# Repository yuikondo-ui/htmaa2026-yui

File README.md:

# htmaa2026-yui

Yui Kondo's documentation site for *How to Make (Almost) Anything* (MIT MAS.863, Fall 2026).

**You write Markdown; `build.py` makes the site.** No framework — one Python script, one
CSS file. GitHub Actions rebuilds and deploys to GitHub Pages on every push to `main`.

## Layout

```
content/
  site.yml            name, banner text, email, repo link
  about.md            About page (two columns; split with a line containing only ---)
  final.md            Final project page
  weeks/weekNN.md     one file per week (01–15) — frontmatter + Markdown body
img/weekNN/           photos for that week (hero.jpg shows on the Grid + page top)
img/final/
files/weekNN/         design files (CAD, code, …)
css/style.css         all styling
build.py              Markdown → HTML
index.html grid.html about.html final.html weeks/*.html   ← generated, don't edit by hand
```

## Weekly routine

1. Drop photos into `img/weekNN/`. Keep them small (`sips -Z 1600 img/week01/*.jpg`).
2. Write `content/weeks/weekNN.md`. `##` headings become the left sidebar (見出し); `###` nest under them.
   Reference images as `img/weekNN/photo.jpg` — paths are fixed up for you.
3. Set `status: Done` in the frontmatter when finished.
4. Preview locally: `python3 build.py` then open `index.html`
   (first time: `pip install markdown`).
5. `git add -A && git commit -m "week NN" && git push` — Pages redeploys in ~1 minute.

### Week frontmatter

```
---
week: 03
date: 09/23
topics: [embedded programming](http://academy.cba.mit.edu/classes/embedded_programming/index.html)
recitation: electronics
status: WIP            # or Done
hero: img/week03/hero.jpg
summary: One line shown under the title.
---
```

`topics` (the class topics, with links) shows in the Index's middle column, the Grid caption
and the page's meta line. Optional `title:` adds your own name for the week to the page
heading (“Week 3 / title”); without it the heading is just “Week 3”.

## GitHub Pages setup (once)

Repo → Settings → Pages → *Build and deployment* → Source: **GitHub Actions**.
The workflow in `.github/workflows/pages.yml` does the rest.

## Fonts

| Use | Typeface | Status |
|-----|----------|--------|
| Name "Yui Kondo" in the header | **Gridular** (CoType Foundry, free, CC BY-ND 4.0) | Download from cotypefoundry.com/our-fonts/gridular and save as `fonts/Gridular-Regular.woff2` |
| Everything else | **ABC Diatype Variable** (ABC Dinamo, licensed) | Falls back to **Geist** (then Inter Tight) from Google Fonts unless `fonts/ABCDiatypeVariable.woff2` (+ `-Italic`) is present |
| Red banner | **ABC Diatype Extended Black Italic** | Falls back to **Archivo** Expanded Black Italic unless `fonts/ABCDiatypeExtended-BlackItalic.woff2` is present |

Until Gridular is added the name uses the body face. If your files are `.otf`/`.ttf`, either
change the `url(...)` in `css/style.css` or convert to woff2.
# mirror-extension

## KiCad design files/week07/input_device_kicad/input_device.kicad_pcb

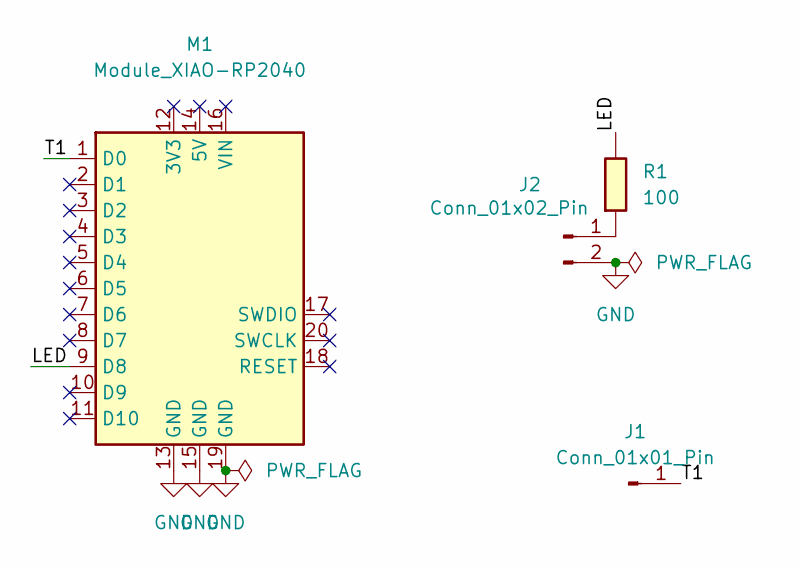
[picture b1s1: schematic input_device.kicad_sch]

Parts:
J1: Conn_01x01_Pin; PinHeader_01x01_P2.54mm_Horizontal_SMD
J2: Conn_01x02_Pin; PinHeader_01x02_P2.54mm_Horizontal_SMD
M1: Module_XIAO-RP2040; SeeedStudio_XIAO_RP2040
R1: 100; R_1206

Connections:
/<NO NET>: M1.10 (D9)
/<NO NET>_1: M1.10 (D9)
/LED: M1.9 (D8), R1.1
/T1: J1.1 (Pin_1_1), M1.1 (D0)
GND: J2.2, M1.13 (GND), M1.15 (GND), M1.19 (GND)
unnamed: J2.1, R1.2

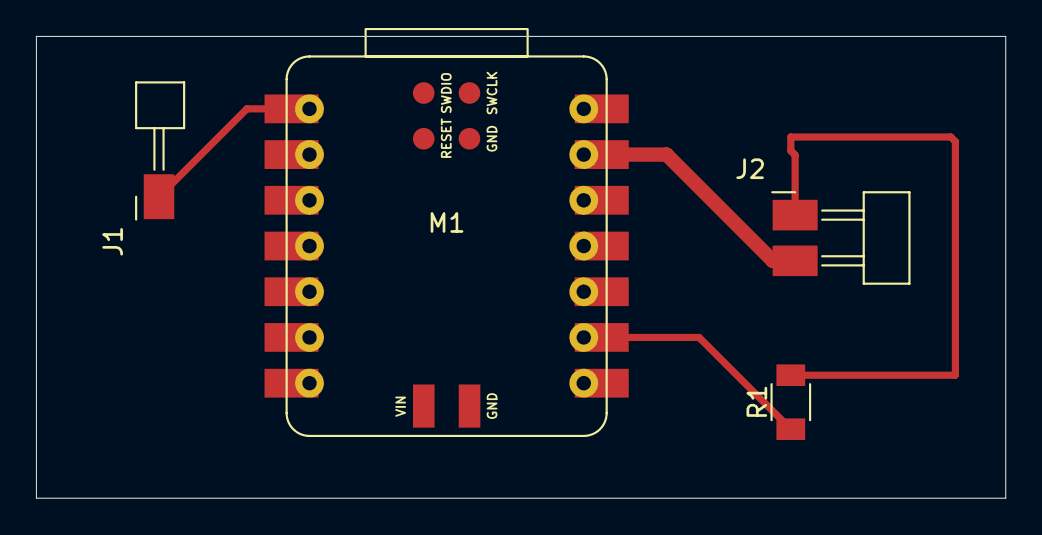
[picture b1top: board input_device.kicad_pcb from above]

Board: 2 copper layers, 53.8 x 25.7 mm, 4 parts (0 on the bottom side), 4 nets.

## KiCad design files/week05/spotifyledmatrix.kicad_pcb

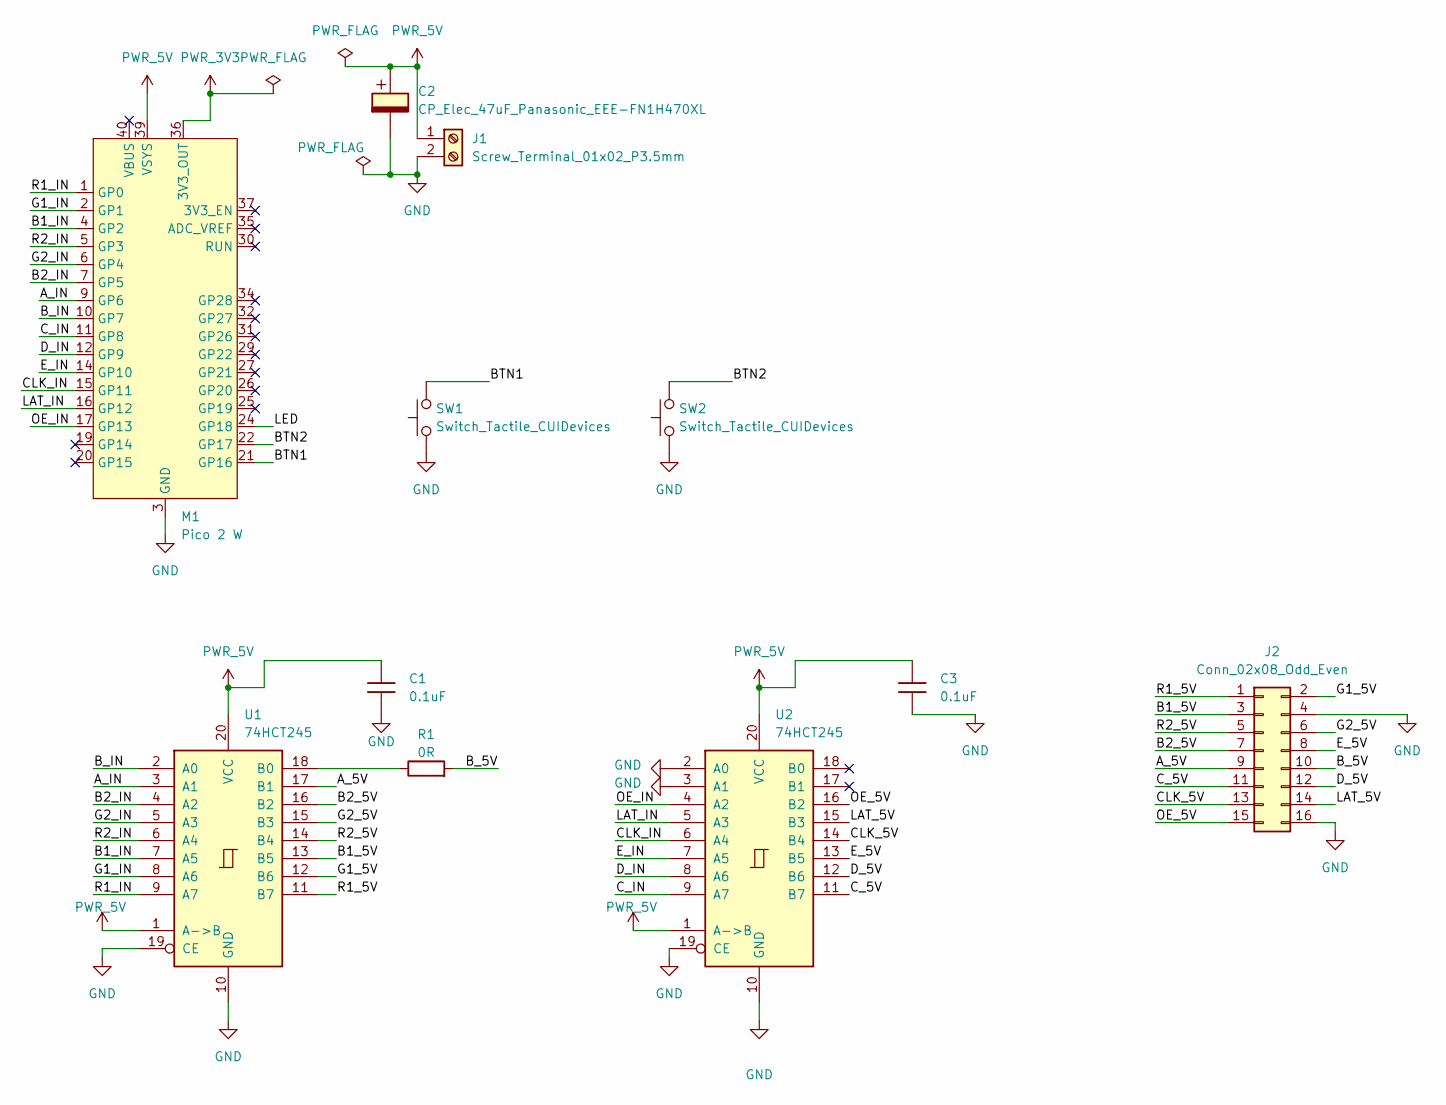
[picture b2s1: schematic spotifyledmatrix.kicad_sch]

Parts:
C1, C3: 0.1uF; C_1206
C2: CP_Elec_47uF_Panasonic_EEE-FN1H470XL
J1: Screw_Terminal_01x02_P3.5mm; TerminalBlock_OnShore_1x02_P3.50mm_Horizontal
J2: Conn_02x08_Odd_Even; PinHeader_2x08_P2.54mm_Vertical
M1: Pico 2 W; RaspberryPi_PicoW_Combined
R1: 0R; R_1206_3216Metric
SW1, SW2: Switch_Tactile_CUIDevices; Button_CUIDevices_TS04-66-43-BK-260-SMT_6.0x6.0mm
U1, U2: 74HCT245; DIP-20_W7.62mm_LongPads

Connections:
/A_5V: J2.9, U1.17 (B1)
/A_IN: M1.9 (GP6), U1.3 (A1)
/B1_5V: J2.3, U1.13 (B5)
/B1_IN: M1.4 (GP2), U1.7 (A5)
/B2_5V: J2.7, U1.16 (B2)
/B2_IN: M1.7 (GP5), U1.4 (A2)
/BTN1: M1.21 (GP16), SW1.3, SW1.4
/BTN2: M1.22 (GP17), SW2.3, SW2.4
/B_5V: J2.10, R1.2
/B_IN: M1.10 (GP7), U1.2 (A0)
/CLK_5V: J2.13, U2.14 (B4)
/CLK_IN: M1.15 (GP11), U2.6 (A4)
/C_5V: J2.11, U2.11 (B7)
/C_IN: M1.11 (GP8), U2.9 (A7)
/D_5V: J2.12, U2.12 (B6)
/D_IN: M1.12 (GP9), U2.8 (A6)
/E_5V: J2.8, U2.13 (B5)
/E_IN: M1.14 (GP10), U2.7 (A5)
/G1_5V: J2.2, U1.12 (B6)
/G1_IN: M1.2 (GP1), U1.8 (A6)
/G2_5V: J2.6, U1.15 (B3)
/G2_IN: M1.6 (GP4), U1.5 (A3)
/LAT_5V: J2.14, U2.15 (B3)
/LAT_IN: M1.16 (GP12), U2.5 (A3)
/LED: M1.24 (GP18)
/OE_5V: J2.15, U2.16 (B2)
/OE_IN: M1.17 (GP13), U2.4 (A2)
/R1_5V: J2.1, U1.11 (B7)
/R1_IN: M1.1 (GP0), U1.9 (A7)
/R2_5V: J2.5, U1.14 (B4)
/R2_IN: M1.5 (GP3), U1.6 (A4)
GND: C1.2, C2.2, C3.2, J1.2, J2.4, J2.16, M1.3 (GND), M1.8 (GND), M1.13 (GND), M1.18 (GND), M1.23 (GND), M1.28 (GND), M1.33 (GND), M1.38 (GND), SW1.1, SW1.2, SW2.1, SW2.2, U1.10 (GND), U1.19 (CE), U2.2 (A0), U2.3 (A1), U2.10 (GND), U2.19 (CE)
unnamed: R1.1, U1.18 (B0)
PWR_3V3: M1.36 (3V3_OUT)
PWR_5V: C1.1, C2.1, C3.1, J1.1, M1.39 (VSYS), U1.1 (A->B), U1.20 (VCC), U2.1 (A->B), U2.20 (VCC)

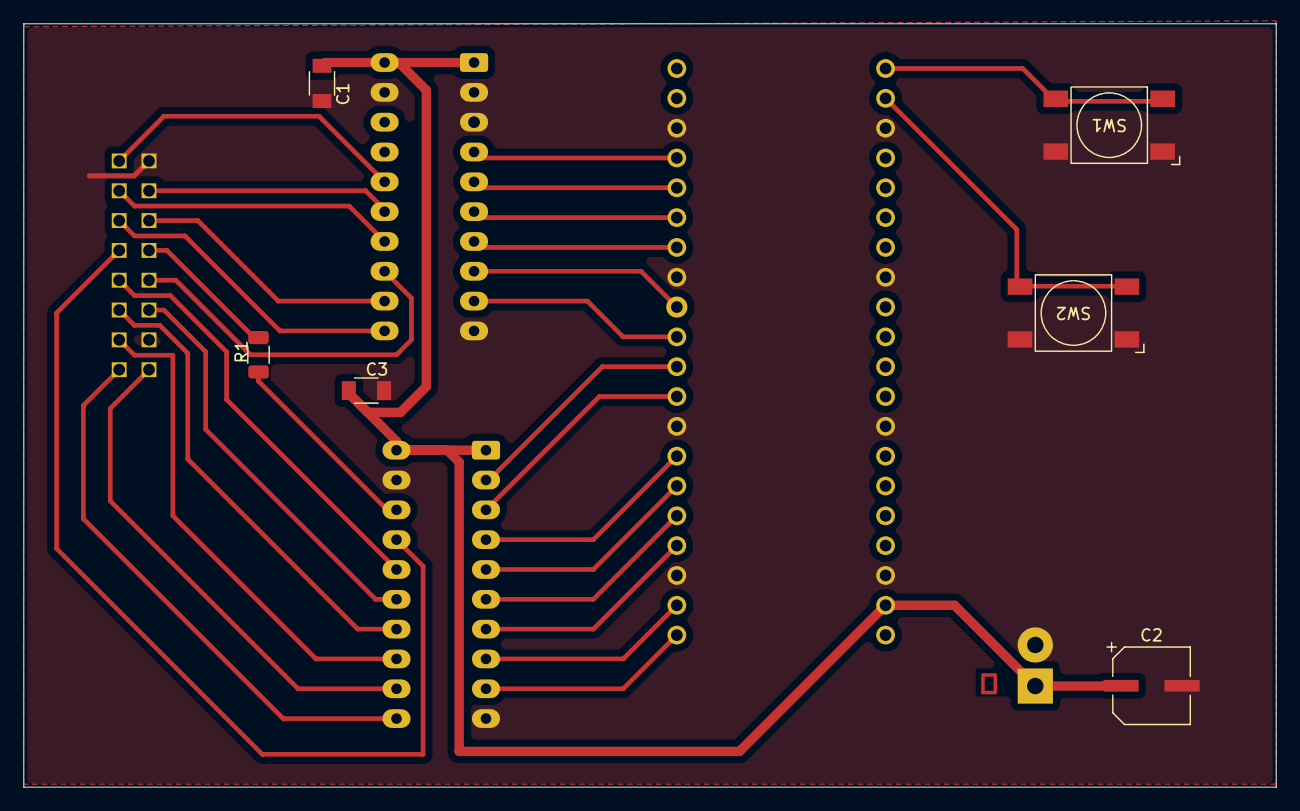
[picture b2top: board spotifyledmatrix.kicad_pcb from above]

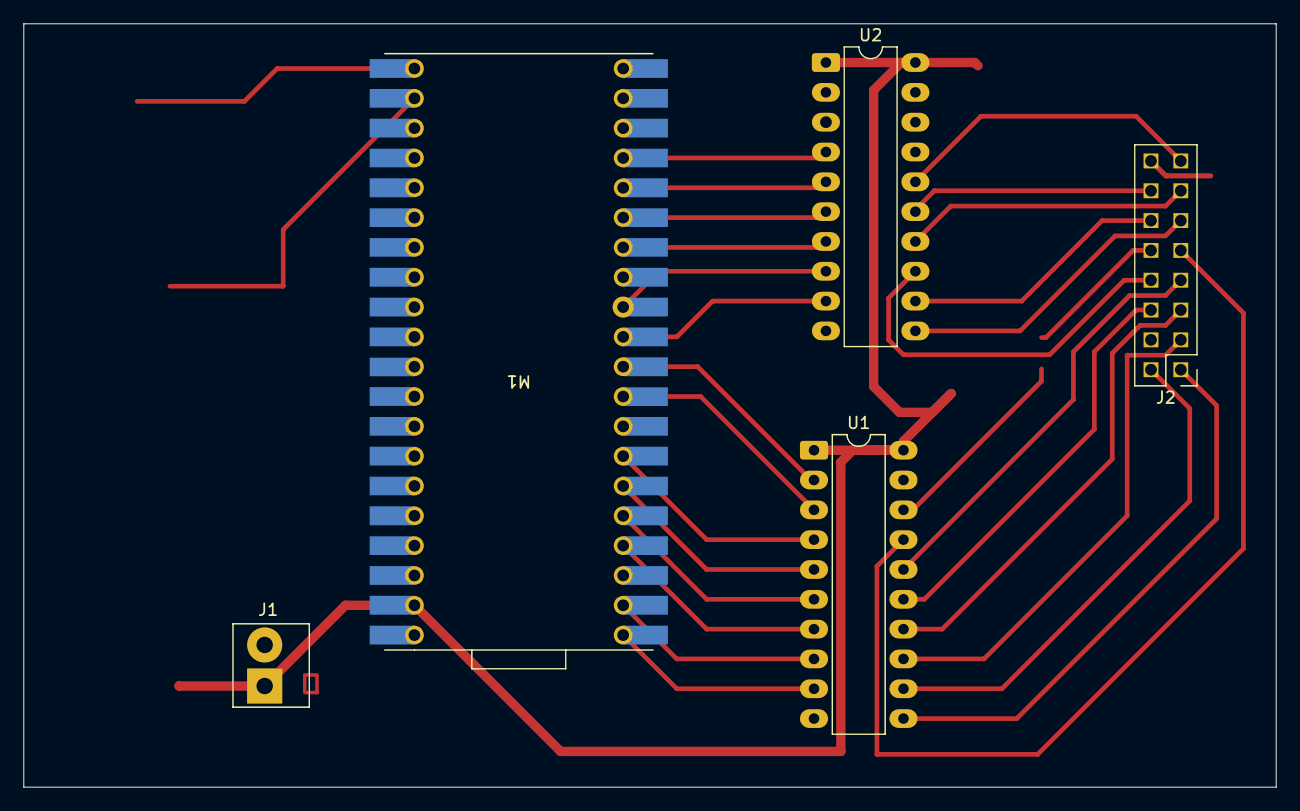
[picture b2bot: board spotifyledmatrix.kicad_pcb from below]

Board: 2 copper layers, 106.7 x 65.0 mm, 11 parts (5 on the bottom side), 33 nets.
